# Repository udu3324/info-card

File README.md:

# Info Card PCB

A pcb in the shape of a standard size credit card with nft reading/writing capabilities, contact information, and useful references on the back. It is **fully designed in KiCad** instead of EasyEDA with symbols/footprints sourced from Ultralibrarian. 

## Why I Made It

I wanted to take a notch down on all the highly complicated PCBs I've made and create something more artsy. I gained more experience from using Krita with its keybinds and workflow.

## Schematic

It's really simple. I don't think you can run anything else from NFC but a few components.

## BOM
It's the tariffs and shipping that got me. See more detail [here](https://github.com/udu3324/info-card/blob/main/JOURNAL.md#july-23rd-price-shortening) on my efforts of trying to lower the price to fit the grant.

| Price     | Part Number               | Category | LCSC Part | Type   | Designator | Quantity | Manufacturer |
|-----------|---------------------------|----------|-----------|--------|------------|----------|--------------|
| $1.73     | NT3H2111W0FHKH            | Extended | C710403   | System | U1         | 2        | JLCPCB       |
| $0.02     | KT-0805G                  | Basic    | C2297     | System | D1         | 2        | JLCPCB       |
| $0.00     | 0805W8F470JT5E            | Basic    | C17714    | System | R1         | 2        | JLCPCB       |
| $0.02     | CL21B224KBFNNNE           | Basic    | C5378     | System | C1         | 2        | JLCPCB       |
| **$1.77** | **Total in parts**        |          |           |        |            |          |              |
| -----     | JCLPCB Checkout Below     | -----    | -----     | -----  | -----      | -----    | -----        |
| $18.23    | Merchandise Total         | N/A      | N/A       | N/A    | N/A        | N/A      | N/A          |
| $26.03    | Shipping Estimate         | N/A      | N/A       | N/A    | N/A        | N/A      | N/A          |
| $10.04    | Customs duties & taxes    | N/A      | N/A       | N/A    | N/A        | N/A      | N/A          |
| $0.50     | Payment fee               | N/A      | N/A       | N/A    | N/A        | N/A      | N/A          |
| $3.69     | Sales Tax                 | N/A      | N/A       | N/A    | N/A        | N/A      | N/A          |
| **$58.49**| **Grand Total**           |          |           |        |            |          |              |

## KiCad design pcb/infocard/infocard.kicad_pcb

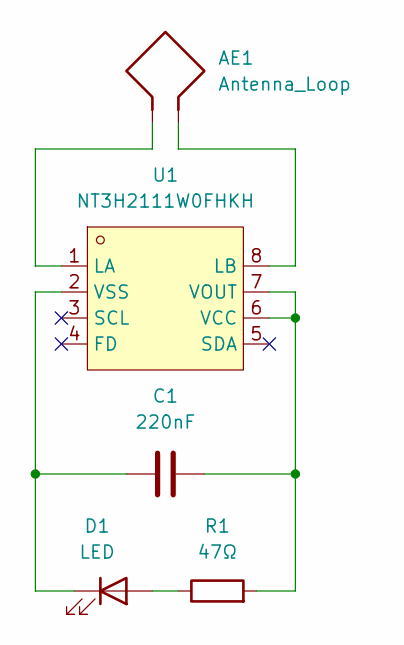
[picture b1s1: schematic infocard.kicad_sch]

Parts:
AE1: Antenna_Loop; card_nfc
C1: 220nF; C_0805_2012Metric_Pad1.18x1.45mm_HandSolder
D1: LED; LED_0805_2012Metric
R1: 47Ω; R_0805_2012Metric_Pad1.20x1.40mm_HandSolder
U1: NT3H2111W0FHKH; XQFN-8_L1.6-W1.6-P0.50-BL_NT3H2111W0FHKH; LCSC Part C710403

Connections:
unnamed: D1.2 (A), R1.1
unnamed: C1.1, D1.1 (K), U1.2 (VSS)
unnamed: AE1.1, U1.1 (LA)
unnamed: AE1.2, U1.8 (LB)
unnamed: C1.2, R1.2, U1.6 (VCC), U1.7 (VOUT)

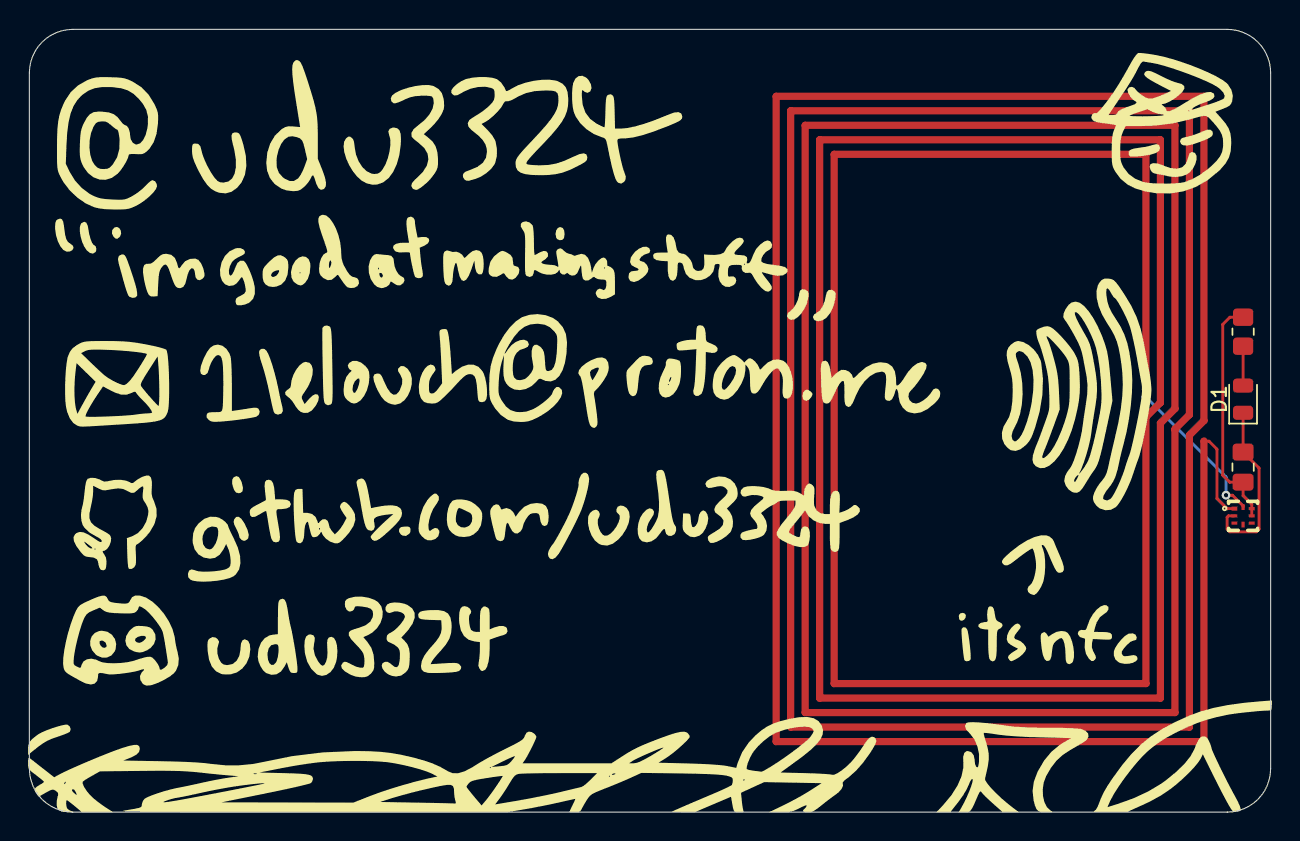
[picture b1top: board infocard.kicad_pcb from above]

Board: 2 copper layers, 85.6 x 54.0 mm, 5 parts (0 on the bottom side), 5 nets.

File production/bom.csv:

Designator,Footprint,Quantity,Value,LCSC Part #
AE1,card_nfc,1,Antenna_Loop,
C1,0805,1,220nF,
D1,0805,1,LED,
R1,0805,1,47Ω,
U1,XQFN-8_L1.6-W1.6-P0.50-BL_NT3H2111W0FHKH,1,NT3H2111W0FHKH,C710403

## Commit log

2025-07-22 init upload
2025-07-23 more stuff
2025-07-23 add everything else
